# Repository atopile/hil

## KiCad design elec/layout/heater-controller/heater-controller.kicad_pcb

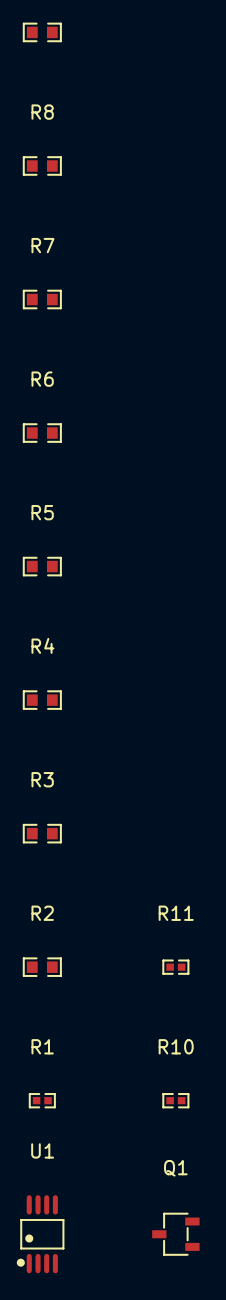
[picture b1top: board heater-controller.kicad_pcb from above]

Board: 2 copper layers, 13 parts (0 on the bottom side), 12 nets, no tracks yet.

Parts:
Q1: SOT-23-3_L2.9-W1.6-P1.90-LS2.8-BR-186170
R1: 1MΩ ±1% 62.5mW; R0402-56259e
R2, R3, R4, R5, R6, R7, R8, R9: 22Ω ±1% 100mW; R0603-ebcab9
R10, R11: 10kΩ ±1% 62.5mW; R0402-56259e
U1: VSSOP-8_L3.0-W3.0-P0.65-LS4.9-BL-beff67

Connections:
IN1plus: R1.2, U1.3
OUT1: R1.1, R10.1, R11.1, U1.1
gate: Q1.1, R10.2
gnd: Q1.2, R11.2
gnd-1: Q1.3, R9.2
net: R3.2, R4.1
net-1: R7.2, R8.1
net-2: R4.2, R5.1
net-3: R2.2, R3.1
net-4: R8.2, R9.1
net-5: R6.2, R7.1
net-6: R5.2, R6.1

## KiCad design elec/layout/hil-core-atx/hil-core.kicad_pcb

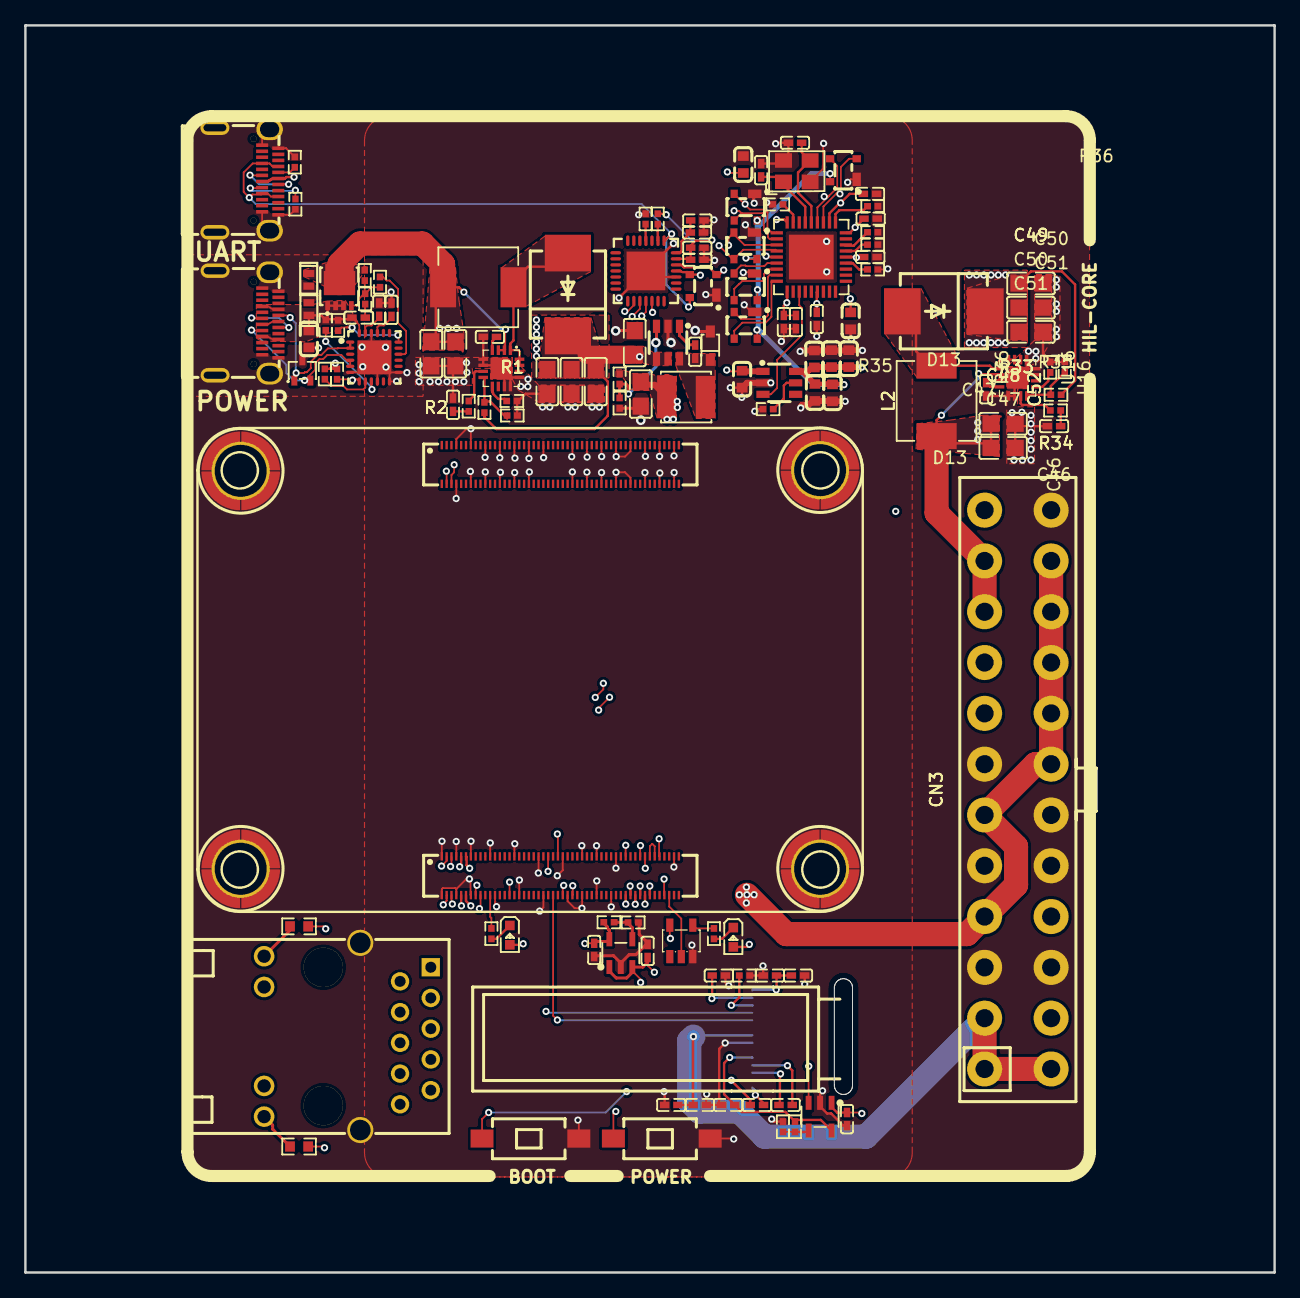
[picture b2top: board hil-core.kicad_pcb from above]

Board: 4 copper layers, 103.3 x 103.1 mm, 130 parts (0 on the bottom side), 100 nets.

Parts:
C1, C46: 6.8nF ±10% 50V X7R; C0402-b3ef17
C2, C3, C4, C5, C6, C10, C47, C48, C49, C50, C51: 10µF ±10% 25V X5R; C0805-3b2e55
C7, C18, C29, C52: 4.7µF ±20% 10V X5R; C0402-b3ef17
C8: 470nF ±20% 16V X5R; C0402-b3ef17
C9: 4.7µF ±10% 25V X5R; C0805-3b2e55
C11, C12, C13, C14, C15, C16, C23, C24, C27: 1µF ±10% 25V X5R; C0402-b3ef17
C17, C19, C20, C21, C25, C26, C28, C32, C33, C34, C35, C36, C37: 100nF ±10% 16V X7R; C0402-b3ef17
C22: 4.7µF ±10% 35V X5R; C0603-bd72f6
C30, C31, C40, C41, C42, C43, C44, C45: 10µF ±10% 10V X5R; C0603-bd72f6
C38, C39: 20pF ±5% 50V C0G; C0402-b3ef17
CN1, CN2: CONN-SMD_DF40C-100DS-0.4V-51-ceffa9
CN3: CONN-TH_39281243-998840
D1, D13: SMC_L7.1-W6.2-LS8.1-RD-d9649d
D2: LED0603-RD-YELLOW-5af84a
D3: LED0603-RD-c81ffb
D4: SOT-323-3_L2.1-W1.3-P1.32-LS2.1-BR-ee9edb
D5, D6: DFN1610-2_L1.6-W1.0-P1.05-RD-57a24e
D7, D8, D9, D10, D11, D12: SOT-143_L2.9-W1.3-P1.92-LS2.3-BR-44397f
L1, L2: IND-SMD_L7.1-W6.6-48b69f
OLED1: OLED-SMD_N087-2832TSWYG02-H14_1-7d3a70
Q1: PDFN3333-8_L3.1-W3.2-P0.65-LS3.4-BL-33e04e
R1, R5, R14, R23, R33: 10kΩ ±1% 62.5mW; R0402-56259e
R2, R34: 180kΩ ±1% 62.5mW; R0402-56259e
R3, R35: 2.49kΩ ±1% 62.5mW; R0402-56259e
R4, R36: 75kΩ ±1% 62.5mW; R0402-56259e
R6: 56kΩ ±1% 62.5mW; R0402-56259e
R7, R8: 2kΩ ±1% 62.5mW; R0402-56259e
R9, R10: 470Ω ±1% 100mW; R0603-ebcab9
R11, R16, R19: 1kΩ ±1% 62.5mW; R0402-56259e
R12: 1.8kΩ ±1% 62.5mW; R0402-56259e
R13: 510kΩ ±1% 62.5mW; R0402-56259e
R15: 25.5kΩ ±1% 62.5mW; R0402-56259e
R17, R18, R24: 4.7kΩ ±1% 62.5mW; R0402-56259e
R20: 100kΩ ±1% 62.5mW; R0402-56259e
R21: 22kΩ ±1% 62.5mW; R0402-56259e
R22: 100Ω ±1% 62.5mW; R0402-56259e
R25, R26, R28, R29: 33kΩ ±1% 62.5mW; R0402-56259e
R27: 12kΩ ±1% 62.5mW; R0402-56259e
R30: 15kΩ ±1% 62.5mW; R0402-56259e
R31, R32: 5.1kΩ ±1% 62.5mW; R0402-56259e
RJ1: RJ45-TH_HR911130A-5845d4
SW1, SW2: SW-SMD_L6.0-W3.3-LS8.0-cfbaed
U1, U16: VQFN-16_L3.0-W3.0-P0.50-BL-EP1.7-62c35a
U2: SOD-323_L1.8-W1.3-LS2.5-RD
U3: SOT-23-6_L2.9-W1.6-P0.95-LS2.8-BR
U4: 10µH ±20%; IND-SMD_L4.0-W4.0
U5: SOT-23-5_L3.0-W1.7-P0.95-LS2.8-BR-9d80aa
U6, U7, U8, U9: SMD_BD5.6-D4.1-12eb58
U10, U11: SOT-23-5_L3.0-W1.7-P0.95-LS2.8-BL
U12: QFN-24_L4.0-W4.0-P0.50-BL-EP2.8-2a85a7
U13: WQFN-28_L5.0-W5.0-P0.50-BL-EP3.2-79d8c5
U14: SQFN-36_L6.0-W6.0-P0.50-BL-EP-5817ac
U15: SOT-23-6_L2.9-W1.6-P0.95-LS2.8-BR-bfc73b
USB1, USB2: USB-C-SMD_TYC-324G-a50b79
X1: CRYSTAL-SMD_4P-L3.2-W2.5-BL-1-d85bc6

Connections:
B5: R32.1, USB2.B5
C1N: C13.1, OLED1.4
C1P: C13.2, OLED1.3
C2N: C14.1, OLED1.2
C2P: C14.2, OLED1.1
CB: C8.1, U3.1
CC1: R31.1, USB2.A5
DISCH: R16.2, U12.9
DN2: USB1.A7, USB1.B7
DP2: USB1.A6, USB1.B6
EN_ENh: U14.12, U15.3
GND: C1.2, C2.2, C3.2, C4.2, C5.2, C6.2, C7.2, C9.2, C10.2, C11.2, C12.2, C15.2, C16.2, C17.2, C18.2, C19.2, C20.2, C21.2, C22.1, C23.1, C24.1, C26.2, C27.2, C28.2, C29.2, C30.2, C31.2, C32.2, C33.2, C34.2, C35.2, C36.2, C37.2, C38.2, C39.2, C40.2, C41.2, C42.2, C43.2, C44.2, C45.2, C46.2, C47.2, C48.2, C49.2, C50.2, C51.2, C52.2, CN1.1, CN1.4, CN1.7, CN1.11, CN1.16, CN1.21, CN1.26, CN1.30, CN1.33, CN1.37, CN1.49, CN1.65, CN1.68, CN1.71, CN1.74, CN1.79, CN1.84, CN1.89, CN1.94, CN1.97, CN1.100, CN2.4, CN2.7, CN2.10, CN2.13, CN2.16, CN2.19, CN2.22, CN2.28, CN2.31, CN2.34, CN2.37, CN2.40, CN2.43, CN2.46, CN2.49, CN2.52, CN2.55, CN2.58, CN2.61, CN2.64, CN2.67, CN2.70, CN2.73, CN2.82, CN2.85, CN2.88, CN2.91, CN2.94, CN2.97, CN3.3, CN3.5, CN3.7, CN3.15, CN3.17, CN3.18, CN3.24, D4.3, D5.2, D6.2, D7.1, D8.1, D9.1, D10.1, D11.1, D12.1, OLED1.7, R1.2, R4.2, R5.2, R11.2, R13.2, R14.2, R23.2, R25.2, R26.2, R27.2, R28.2, R29.2, R30.2, R31.2, R32.2, R33.2, R36.2, RJ1.SHIELD0, RJ1.SHIELD1, SW1.2, SW2.2, U1.5, U1.6, U1.11, U1.12, U1.13, U1.17, U2.2, U3.2, U5.3, U6.1, U6.2, U6.3, U6.4, U7.1, U7.2, U7.3, U7.4, U8.1, U8.2, U8.3, U8.4, U9.1, U9.2, U9.3, U9.4, U10.2, U11.2, U12.6, U12.10, U12.12, U12.13, U12.22, U12.25, U13.3, U13.29, U14.37, U15.2, U16.5, U16.6, U16.11, U16.12, U16.13, U16.17, USB1.1, USB1.2, USB1.3, USB1.4, USB1.A1, USB1.A12, USB1.B1, USB1.B12, USB2.1, USB2.2, USB2.3, USB2.4, USB2.A1, USB2.A12, USB2.B1, USB2.B12, X1.2, X1.4
HS_IND_CFG_SEL1: R28.1, U14.25
ILIM: R30.1, U15.5
IREF: OLED1.12, R13.1
MDI0_: CN1.5, RJ1.P3
MDI1plus: CN1.2, RJ1.P4
MDI2_: CN1.96, RJ1.P6
MDI3_: CN1.98, RJ1.P9
POWER_3V3: C12.1, C20.1, C21.1, C30.1, C31.1, C32.1, C33.1, C34.1, C35.1, C36.1, C37.1, CN3.1, CN3.2, CN3.12, CN3.13, OLED1.8, R12.1, U10.5, U14.5, U14.10, U14.15, U14.23, U14.27, U14.29, U14.36
POWER_5V: C10.1, C11.1, C15.1, C40.1, CN1.57, CN1.58, CN1.59, CN1.60, CN1.61, CN1.62, CN3.4, CN3.6, CN3.19, CN3.20, CN3.21, CN3.22, CN3.23, R6.1, U4.2, U10.1, U10.3, U11.1, U11.3, U15.1
POWER_24V: C4.1, C5.1, C6.1, C9.1, C49.1, C50.1, C51.1, D1.1, D13.1, R2.1, R34.1, U3.4, U3.5
RBIAS: R27.1, U14.35
RSTh: R24.1, U13.9
SCL_SMBCLK_CFG_SEL0: R25.1, U14.24
SDA_SMBBATA_NON_REM1: R26.1, U14.22
SUSPENDh: R23.1, U13.11
SUSP_IND_LOCAL_PWR_NON_REM0: R29.1, U14.28
SW: C8.2, U2.1, U3.6, U4.1
USBDM_UP: D12.2, U14.30, USB2.A7, USB2.B7
USBDP_UP: D12.3, U14.31, USB2.A6, USB2.B6
VBUS: D7.4, U13.8, USB2.A4, USB2.A9, USB2.B4, USB2.B9
VBUS_EN_SNK: R21.2, U12.16
VBUS_VS_DISCH: R19.2, U12.18
VCOMH: C19.1, OLED1.13
Y: R8.2, U5.4
boost_24v-COMP: R3.1, U1.7
boost_24v-FB: R1.1, R2.2, U1.8
boost_24v-FREQ: R4.1, U1.9
boost_24v-SS: C7.1, U1.4
boost_24v-net: C1.1, R3.2
boost_24v-switching_node: D1.2, L1.2, U1.1, U1.15, U1.16
boost_24v_atx-COMP: R35.1, U16.7
boost_24v_atx-FB: R33.1, R34.2, U16.8
boost_24v_atx-FREQ: R36.1, U16.9
boost_24v_atx-SS: C52.1, U16.4
boost_24v_atx-net: C46.1, R35.2
boost_24v_atx-switching_node: D13.2, L2.2, U16.1, U16.15, U16.16
buck_5v-FB: R5.1, R6.2, U3.3
controller-pins[2]: CN1.99, RJ1.P8
controller-pins[5]: CN1.3, RJ1.P7
controller-pins[10]: CN1.95, RJ1.P5
controller-pins[11]: CN1.6, RJ1.P2
controller-pins[14]: CN1.93, RJ1.12
controller-pins[16]: CN1.92, RJ1.13
controller-pins[92]: CN1.54, SW1.1
controller.cm5-cathode: D2.1, R7.1
controller.cm5-cathode-1: D3.1, R8.1
controller.cm5-pins[20]: CN1.90, R7.2
controller.cm5-pins[87]: CN1.44, CN1.45
controller.cm5-pins[94]: CN1.53, U5.2
controller.rj45-anode: R9.2, RJ1.11
controller.rj45-anode-1: R10.2, RJ1.14
gate: Q1.4, R20.1, R21.1, R22.1
hv: C17.1, C18.1, OLED1.14
hv-1: C41.1, C42.1, C43.1, C44.1, C45.1, D8.4, D9.4, D10.4, D11.4, D12.4, U15.6
hv-2: C16.1, OLED1.5, R15.1, U11.5
hv-3: CN1.39, CN1.42, CN1.43, D2.2, D3.2, R9.1, R10.1, U5.5
hv-4: C28.1, C29.1, R24.2, U13.6
hv-5: C2.1, C3.1, D6.1, L1.1, Q1.5, Q1.6, Q1.7, Q1.8, Q1.9, R20.2, U1.2, U1.3
hv-6: C47.1, C48.1, CN3.10, CN3.11, L2.1, U16.2, U16.3
hv-7: C26.1, C27.1, U13.7
ldo_3v3-ADJ_NC: R11.1, R12.2, U10.4
line: CN1.77, OLED1.10
line-1: CN1.73, U13.25
line-2: CN1.75, U13.26
line-3: CN1.23, OLED1.11
line-4: CN1.86, U13.24
line-5: CN1.25, U13.23
line-6: D7.2, D8.2, U13.5, U14.1
line-7: D7.3, D8.3, U13.4, U14.2
oled.regulator_4v-ADJ_NC: R14.1, R15.2, U11.4
pins[2]: CN2.99, D9.2, U14.3
pins[4]: CN2.98, D9.3, U14.4
pins[91]: CN1.46, SW2.1
usb_hub-line: D10.3, U14.7
usb_hub-line-1: D10.2, U14.6
usb_hub-line-2: D11.3, U14.9
usb_hub-line-3: D11.2, U14.8
usbpd-VBUS: C22.2, C25.2, D5.1, Q1.1, Q1.2, Q1.3, R16.1, R19.1, U12.24, USB1.A4, USB1.A9, USB1.B4, USB1.B9
usbpd-hv: R17.2, R18.2
usbpd-line: D4.2, U12.4, U12.5, USB1.B5
usbpd-line-1: R18.1, U12.8
usbpd-line-2: R17.1, U12.7
usbpd-line-3: D4.1, U12.1, U12.2, USB1.A5
usbpd.pd_controller-hv: C24.2, U12.23
usbpd.pd_controller-hv-1: C23.2, U12.21
usbpd.pd_controller-net: C25.1, R22.2
xin: C38.1, U14.33, X1.1
xout: C39.1, U14.32, X1.3

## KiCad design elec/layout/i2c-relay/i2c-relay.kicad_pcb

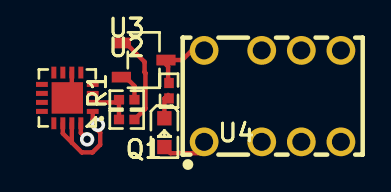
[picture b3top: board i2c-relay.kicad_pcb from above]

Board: 2 copper layers, 7 parts (0 on the bottom side), 8 nets.

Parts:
Q1: SOT-23-3_L2.9-W1.6-P1.90-LS2.8-BR-186170
R1: 2kΩ ±1% 62.5mW; R0402-56259e
U1: QFN-16_L3.0-W3.0-P0.50-BL-EP1.7-3a4c56
U2: 10kΩ ±1% 62.5mW; R0402-56259e
U3: 1kΩ ±1% 62.5mW; R0402-56259e
U4: LED0603-RD-c81ffb
U6: RELAY-TH_HFDXXX-689a1e

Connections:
RESET: U1.1, U1.14, U1.15
cathode: R1.1, U4.1
gate: Q1.1, U2.2
gnd-1: U1.6, U1.17
gnd-3: Q1.2, U3.2
hv-2: U4.2, U6.1
line: U1.2, U2.1, U3.1
relay-gnd: Q1.3, R1.2, U6.8

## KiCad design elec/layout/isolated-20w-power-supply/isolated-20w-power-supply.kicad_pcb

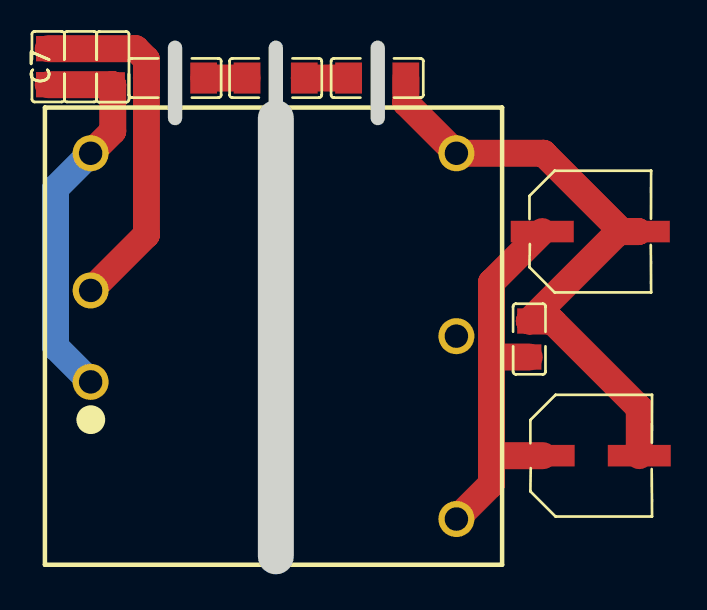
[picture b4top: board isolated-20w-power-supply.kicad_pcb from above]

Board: 2 copper layers, 10 parts (0 on the bottom side), 6 nets.

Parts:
C1, C2: 10µF ±10% 50V X5R; C0805-3b2e55
C3, C7: 1µF ±10% 50V X7R; C0805-3b2e55
C4, C8: 100µF ±20%; CAP-SMD_BD6.3-L6.6-W6.6-FD-3e301d
C5, C6, C9: 2.2nF ±10% 1kV X7R; C1206-f0a137
U1: PWRM-TH_TDPOWER_TDK20-XXSXXWH-ae86e0

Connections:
gnd: C3.2, C4.2, C8.2, C9.2, U1.4
gnd-1: C1.2, C2.2, C5.1, C7.2, U1.2
hv: C3.1, C4.1, C8.1, U1.6
hv-1: C1.1, C2.1, C7.1, U1.1, U1.3
net: C5.2, C6.1
net-1: C6.2, C9.1

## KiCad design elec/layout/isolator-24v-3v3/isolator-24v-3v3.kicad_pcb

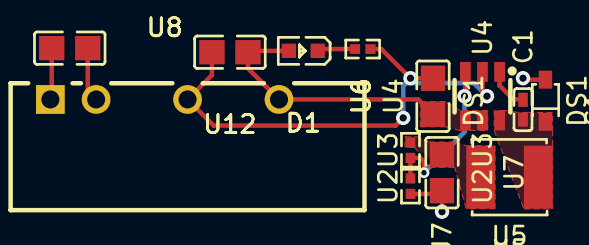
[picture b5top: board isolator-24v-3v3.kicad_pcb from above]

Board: 2 copper layers, 13 parts (0 on the bottom side), 10 nets.

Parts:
C1: 470nF ±20% 16V X5R; C0402-b3ef17
D1: LED0603-RD-c81ffb
DS1: SOD-323_L1.8-W1.3-LS2.5-RD
R1: 1kΩ ±1% 62.5mW; R0402-56259e
U2, U3: 10kΩ ±1% 62.5mW; R0402-56259e
U4: SOT-23-6_L2.9-W1.6-P0.95-LS2.8-BR
U5: 10µH ±20%; IND-SMD_L4.0-W4.0
U6: 4.7µF ±10% 25V X5R; C0805-3b2e55
U7, U12: 10µF ±10% 25V X5R; C0805-3b2e55
U8: PWRM-TH_BXXXXS-2WR2-87119e
U9: 2.2µF ±10% 25V X7R; C0805-3b2e55

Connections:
CB: C1.1, U4.1
FB: U2.1, U3.2, U4.3
SW: C1.2, DS1.1, U4.6, U5.1
cathode: D1.1, R1.1
gnd: U8.2, U9.2
gnd-1: R1.2, U4.2, U6.2, U8.4, U12.2
gnd-2: DS1.2, U2.2, U7.2
hv: U8.1, U9.1
hv-1: D1.2, U4.4, U4.5, U6.1, U8.6, U12.1
hv-2: U3.1, U5.2, U7.1

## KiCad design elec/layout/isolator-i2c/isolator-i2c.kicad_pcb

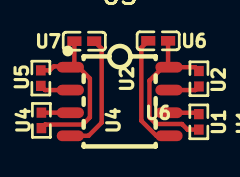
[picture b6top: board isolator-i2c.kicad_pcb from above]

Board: 2 copper layers, 7 parts (0 on the bottom side), 8 nets.

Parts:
U1, U2, U4, U5: 10kΩ ±1% 62.5mW; R0402-56259e
U3: SOIC-8_L4.9-W3.9-P1.27-LS6.0-TL-e13595
U6, U7: 100nF ±10% 16V X7R; C0402-b3ef17

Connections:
gnd: U3.5, U6.2
gnd-1: U3.4, U7.2
hv: U1.2, U2.2, U3.8, U6.1
hv-1: U3.1, U4.2, U5.2, U7.1
line: U1.1, U3.6
line-1: U3.2, U5.1
line-2: U3.3, U4.1
line-3: U2.1, U3.7

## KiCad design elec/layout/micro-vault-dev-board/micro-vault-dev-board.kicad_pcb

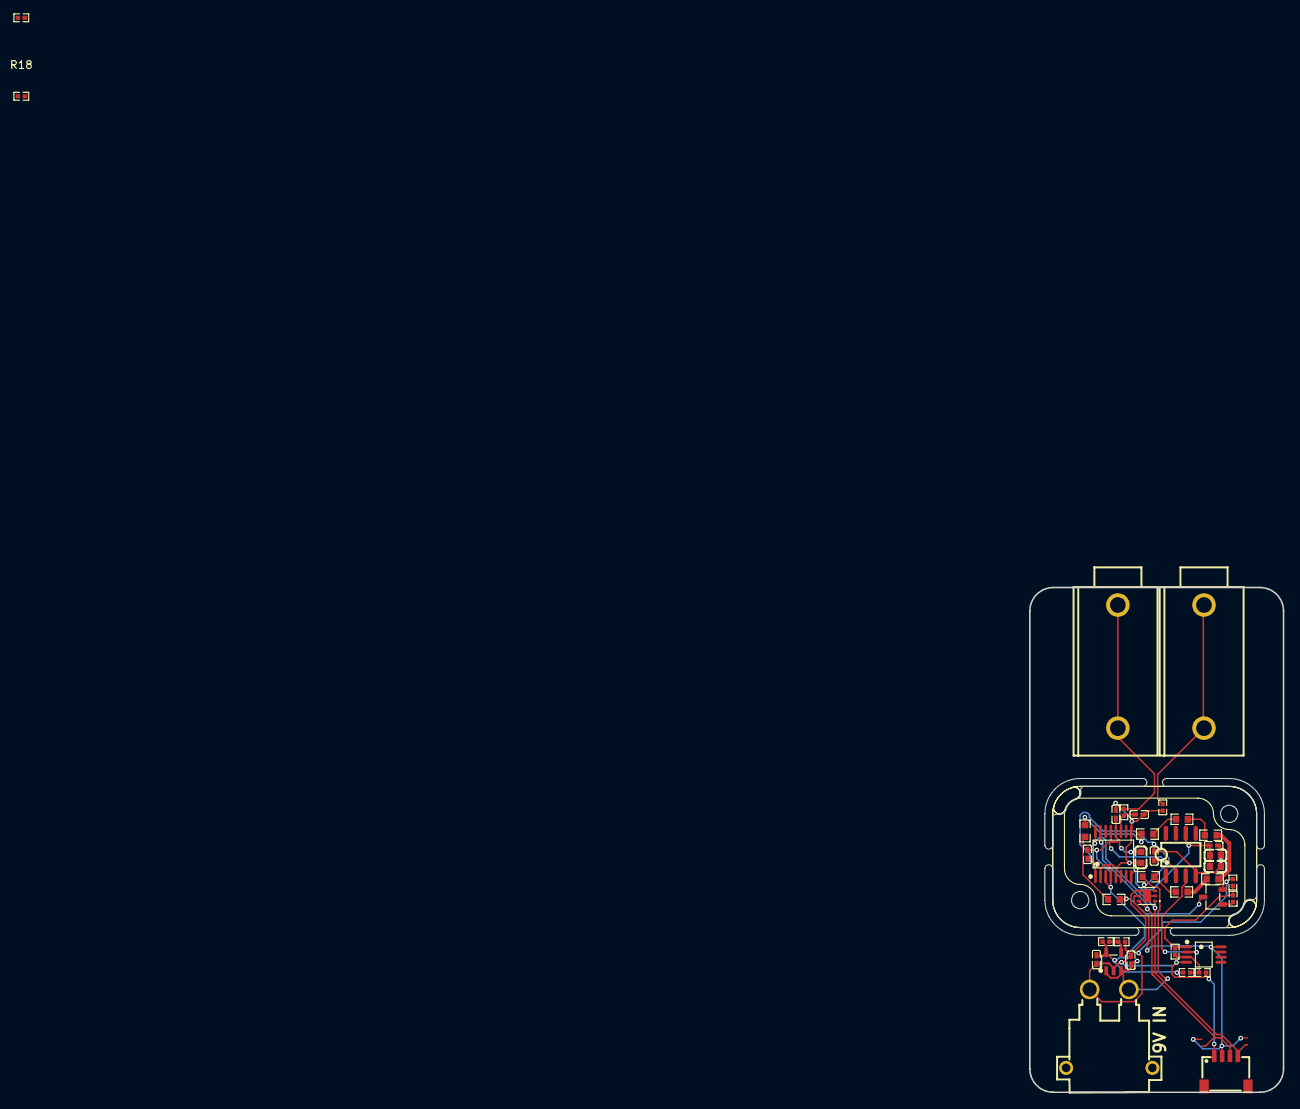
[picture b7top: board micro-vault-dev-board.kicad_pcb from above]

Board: 2 copper layers, 32.3 x 64.4 mm, 41 parts (0 on the bottom side), 24 nets.

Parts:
C1, C3, C10: 100nF ±10% 16V X7R; C0402-b3ef17
C2, C6, C7: 10µF ±10% 10V X5R; C0603-bd72f6
C4, C5, C8, C9: 1µF ±10% 25V X5R; C0402-b3ef17
J1: CONN-TH_XT30PW-M
Q1: SOT-23-3_L2.9-W1.6-P1.90-LS2.8-BR-186170
R1: 1MΩ ±1% 62.5mW; R0402-56259e
R2, R3, R4, R5, R6, R7, R8, R9: 15Ω ±1% 100mW; R0603-ebcab9
R10, R11, R14, R16, R17, R18, R19: 10kΩ ±1% 62.5mW; R0402-56259e
R12: 12kΩ ±1% 62.5mW; R0402-56259e
R13: 88.7kΩ ±0% 62.5mW; R0402-56259e
R15: 36kΩ ±1% 62.5mW; R0402-56259e
U1: CONN-TH_24.243.2-306a6a
U2: CONN-TH_24.243.1_RED-2aff94
U3, U4: NetTie-2_SMD_Pad0.25mm
U5: TSSOP-16_L5.0-W4.4-P0.65-LS6.4-BL-4f6acc
U6: VSSOP-8_L3.0-W3.0-P0.65-LS4.9-BL-beff67
U7: SOIC-8_L5.0-W4.0-P1.27-LS6.0-BL-294f77
U8: SOT-23-5_L3.0-W1.7-P0.95-LS2.8-BL
U9: WSON-6_L2.0-W2.0-P0.65-TL-EP-c93430
X1: CONN-SMD_4P-P1.00_SM04B-SRSS-TB-LF-SN-d36980

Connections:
ADJ_NC: R14.1, R15.2, U8.4
IN1plus: R1.2, R12.1, R13.2, U6.3
OUT1: R1.1, R10.1, R11.1, U6.1
SCL: R18.1, U5.16, U9.1, X1.4
SDA: R19.1, U5.15, U9.6, X1.3
TEMP: U6.2, U7.3
Vplus: R18.2, R19.2, U6.8, U9.5, X1.2
gate: Q1.1, R10.2
gnd: R17.2, U1.1, U1.2
gnd-1: C1.2, C2.2, C3.2, C4.2, C5.2, C6.2, C7.2, C8.2, C9.2, C10.2, J1.1, Q1.2, R11.2, R12.2, R14.2, R17.1, U3.1, U3.2, U5.1, U5.2, U5.4, U5.5, U5.9, U6.4, U7.4, U8.2, U9.2, U9.4, U9.7, X1.1
hv: C8.1, J1.2, R2.1, U8.1, U8.3
hv-1: C3.1, C4.1, C9.1, R13.1, R15.1, U4.2, U5.3, U5.13, U7.2, U8.5
hv-2: C5.1, C6.1, C7.1, U5.8, U7.6
hv-3: C1.1, C2.1, U4.1, U5.12
line: C10.1, R16.2, U5.11
line-1: R16.1, U2.1, U2.2
micro_vault.heater_controller-gnd: Q1.3, R9.2
micro_vault.heater_controller-net: R8.2, R9.1
micro_vault.heater_controller-net-1: R4.2, R5.1
micro_vault.heater_controller-net-2: R7.2, R8.1
micro_vault.heater_controller-net-3: R5.2, R6.1
micro_vault.heater_controller-net-4: R3.2, R4.1
micro_vault.heater_controller-net-5: R6.2, R7.1
micro_vault.heater_controller-net-6: R2.2, R3.1
